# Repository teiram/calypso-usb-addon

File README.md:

# calypso-powerpack-addon (was calypso-usb-addon)
Add-on for the calypso board featuring USB 2.0 hub with 4 ports and 8MB PSRAM

# Description
Based on the inexpensive HS8836A USB 2.0 hub, this add-on provides 4 extra USB ports to connect peripherals to the Calypso board. This could come handy to connect USB keyboards and mice or any other device supported by the Calypso firmware.

It also provides a footprint to install 8MB of extra PSRAM. The PSRAM is addressed using QSPI and was tested to run properly at 108Mhz clock, what would allow to simulate a 8 bit SRAM at around 148 ns access time. Please take into account that version 0.1 has an error in the silk text and iBOM: The PSRAM to use is a ESP32-PSRAM64H.

The board exposes a micro USB connector to connect to the RP2040 with an additional cable (male USB-C to male Micro-USB). But it would be more practical to solder a cable directly to the provided D+/D- pads on the board. You only need two wires for D+/D- since ground is common and the board powers the USB peripherals.

In case you go for the micro-usb connector, try to choose a cable with a thin and short connector on the micro-usb side, because the PS/2 connector blocks don't leave much vertical room to accommodate the cable connector.

For the USB-C side, I recommend to use a connector with presoldered miniboard exposing D+/D-, like the one in the picture.

The board provides power to the USB peripherals coming directly from the Calypso Mini USB port. Take that into account when choosing the power supply for the Calypso board since it must provide enough power for the USB hub and the devices you might connect. 

# Changelog
- 0.1. Initial version
- 0.2. Fix ibom and silk for PSRAM (ESP-PSRAM64H)

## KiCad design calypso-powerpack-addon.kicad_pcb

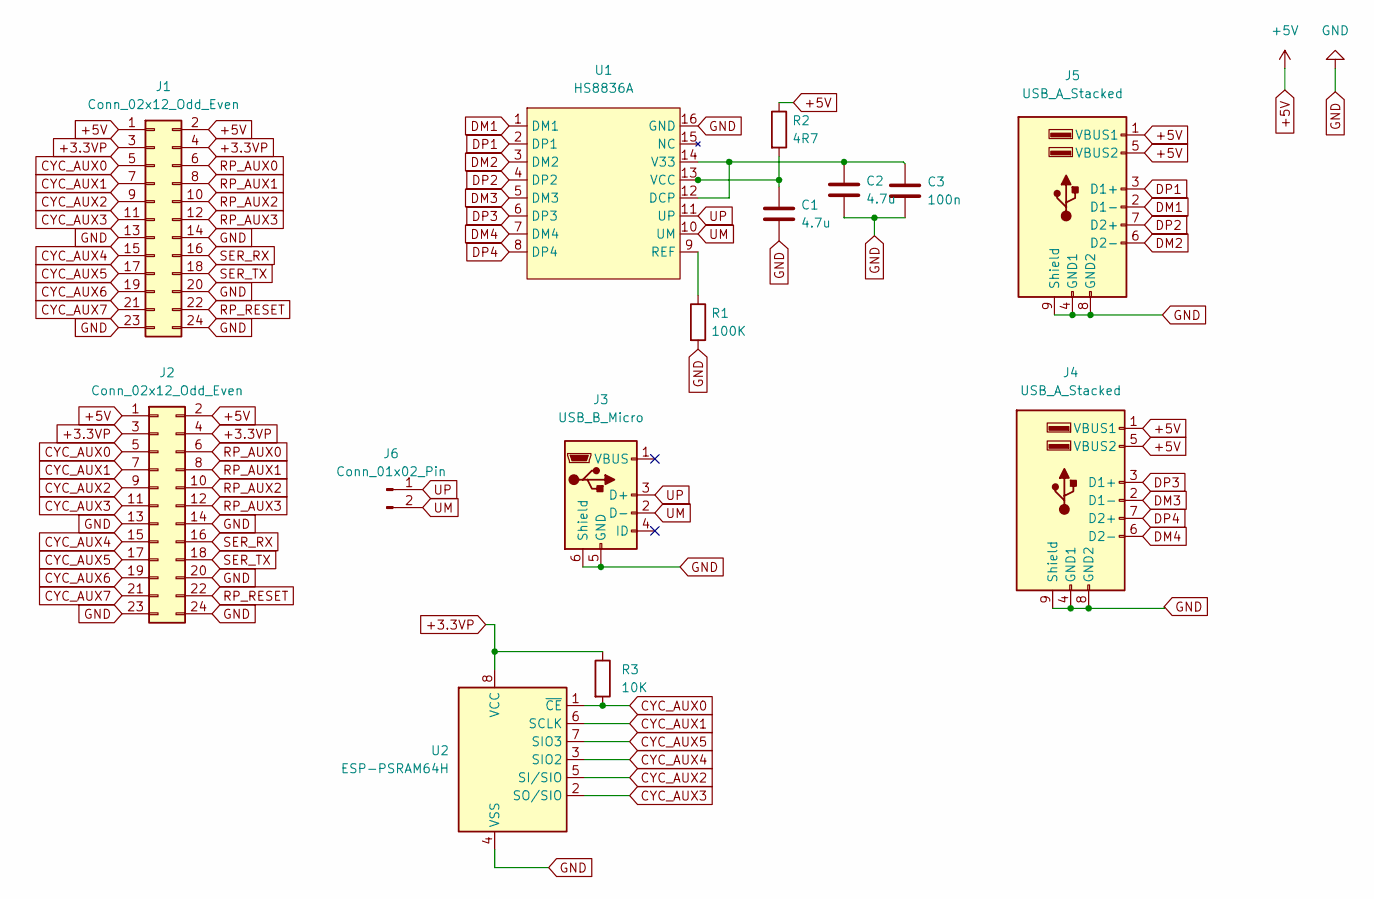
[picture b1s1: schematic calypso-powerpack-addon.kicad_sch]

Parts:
C1, C2: 4.7u; C_1206_3216Metric_Pad1.33x1.80mm_HandSolder
C3: 100n; C_1206_3216Metric_Pad1.33x1.80mm_HandSolder
J1: Conn_02x12_Odd_Even; PinSocket_2x12_P2.54mm_Vertical
J2: Conn_02x12_Odd_Even; PinHeader_2x12_P2.54mm_Vertical
J3: USB_B_Micro; USB_Micro-B_Molex-105017-0001
J4, J5: USB_A_Stacked; USB_A_Wuerth_61400826021_Horizontal_Stacked
J6: Conn_01x02_Pin; PinHeader_1x02_P2.54mm_Vertical
R1: 100K; R_1206_3216Metric_Pad1.30x1.75mm_HandSolder
R2: 4R7; R_1206_3216Metric_Pad1.30x1.75mm_HandSolder
R3: 10K; R_1206_3216Metric_Pad1.30x1.75mm_HandSolder
U1: HS8836A; SOP-16_3.9x9.9mm_P1.27mm
U2: ESP-PSRAM64H; SOIC-8_3.9x4.9mm_P1.27mm

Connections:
+3.3VP: J1.3, J1.4, J2.3, J2.4, R3.1, U2.8 (VCC)
+5V: J1.1, J1.2, J2.1, J2.2, J4.1 (VBUS1), J4.5 (VBUS2), J5.1 (VBUS1), J5.5 (VBUS2), R2.1
CYC_AUX0: J1.5, J2.5, R3.2, U2.1 (~CE)
CYC_AUX1: J1.7, J2.7, U2.6 (SCLK)
CYC_AUX2: J1.9, J2.9, U2.5 (SI/SIO)
CYC_AUX3: J1.11, J2.11, U2.2 (SO/SIO)
CYC_AUX4: J1.15, J2.15, U2.3 (SIO2)
CYC_AUX5: J1.17, J2.17, U2.7 (SIO3)
CYC_AUX6: J1.19, J2.19
CYC_AUX7: J1.21, J2.21
DM1: J5.2 (D1-), U1.1 (DM1)
DM2: J5.6 (D2-), U1.3 (DM2)
DM3: J4.2 (D1-), U1.5 (DM3)
DM4: J4.6 (D2-), U1.7 (DM4)
DP1: J5.3 (D1+), U1.2 (DP1)
DP2: J5.7 (D2+), U1.4 (DP2)
DP3: J4.3 (D1+), U1.6 (DP3)
DP4: J4.7 (D2+), U1.8 (DP4)
GND: C1.2, C2.2, C3.2, J1.13, J1.14, J1.20, J1.23, J1.24, J2.13, J2.14, J2.20, J2.23, J2.24, J3.5 (GND), J3.6 (Shield), J4.4 (GND1), J4.8 (GND2), J4.9 (Shield), J5.4 (GND1), J5.8 (GND2), J5.9 (Shield), R1.2, U1.16 (GND), U2.4 (VSS)
unnamed: C2.1, C3.1, U1.12 (DCP), U1.14 (V33)
unnamed: R1.1, U1.9 (REF)
unnamed: C1.1, R2.2, U1.13 (VCC)
RP_AUX0: J1.6, J2.6
RP_AUX1: J1.8, J2.8
RP_AUX2: J1.10, J2.10
RP_AUX3: J1.12, J2.12
RP_RESET: J1.22, J2.22
SER_RX: J1.16, J2.16
SER_TX: J1.18, J2.18
UM: J3.2 (D-), J6.2, U1.10 (UM)
UP: J3.3 (D+), J6.1, U1.11 (UP)

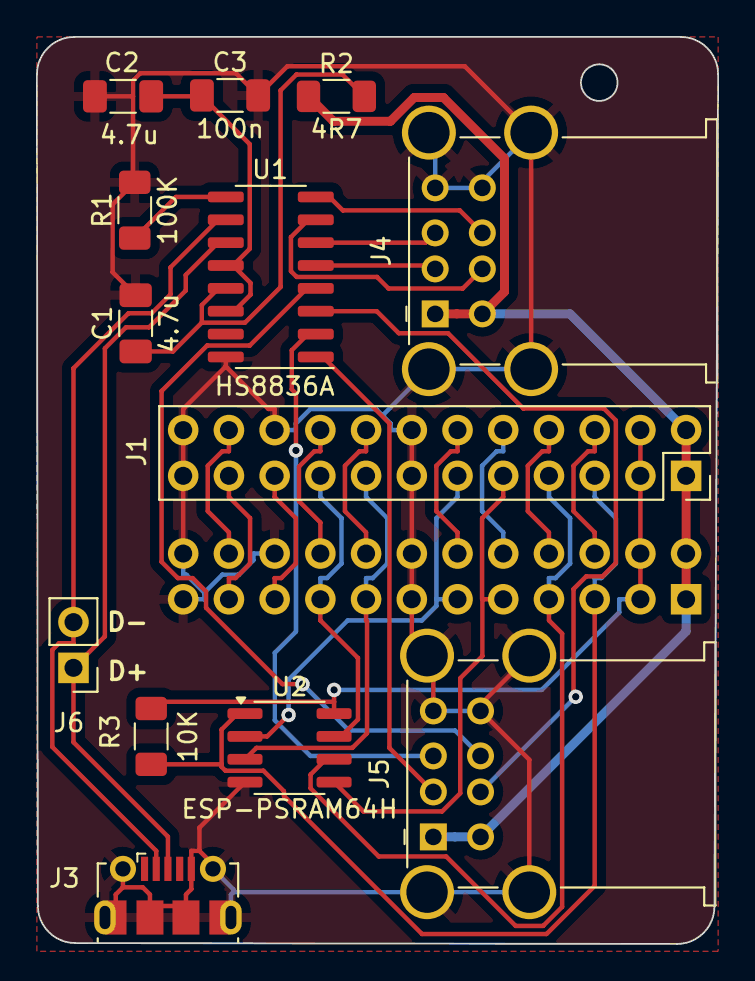
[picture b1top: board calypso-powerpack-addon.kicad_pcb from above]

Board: 2 copper layers, 37.8 x 50.4 mm, 14 parts (1 on the bottom side), 31 nets.

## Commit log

2026-01-26 Fix PSRAM chip id
